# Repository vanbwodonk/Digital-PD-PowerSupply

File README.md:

# Digital USB-PD Power Supply

Low Cost USB Power Delivery adjustable power supply using CH32X035 RISC-V MCU.

- **MCU:** CH32X035G8U6 (WQFN-28), 48MHz RISC-V, USB PD PHY, USB 2.0 FS
- **Power:** USB Type-C PD (sink) → adjustable output voltage/current
- **Peripherals:** Rotary encoder control, OLED display, INA219 current sensing, USB CDC serial
- **Firmware:** C with ch32v003fun framework, PlatformIO build
- **Hardware:** Custom WQFN-28 dev board (KiCad design in `Hardware/`)

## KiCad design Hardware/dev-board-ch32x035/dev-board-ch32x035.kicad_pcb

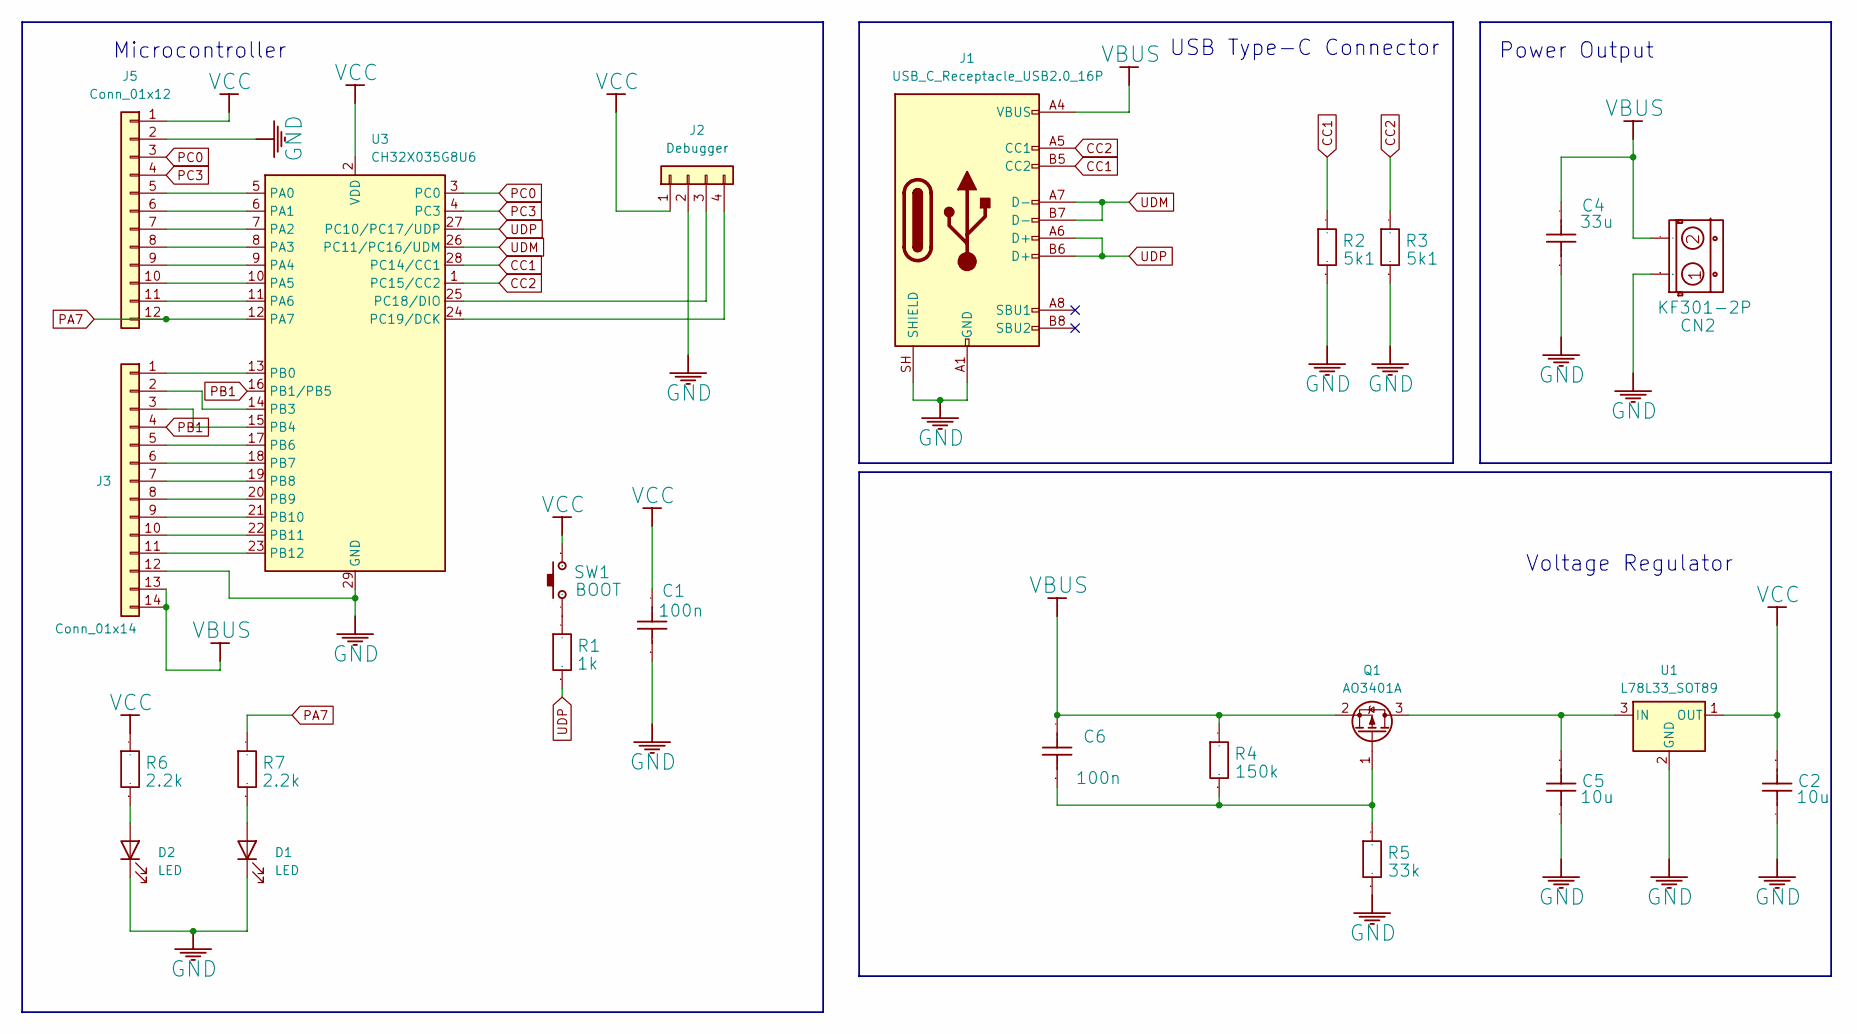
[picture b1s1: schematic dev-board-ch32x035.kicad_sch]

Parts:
C1, C6: 100n; C_0805_2012Metric; Manufacturer Part CC0603KRX7R9BB104
C2, C5: 10u; C_1206_3216Metric; Manufacturer Part CL10A106KP8NNNC
C4: 33u; C_1812_4532Metric; Manufacturer Part CC0603KRX7R9BB104
CN2: KF301-2P; TerminalBlock_Phoenix_MKDS-1,5-2-5.08_1x02_P5.08mm_Horizont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; Manufacturer Part KF301-5.0-2P
D1, D2: LED; LED_0805_2012Metric
J1: USB_C_Receptacle_USB2.0_16P; USB_C_Receptacle_GCT_USB4105-xx-A_16P_TopMnt_Horizontal
J2: Debugger; PinHeader_1x04_P2.54mm_Vertical
J3: Conn_01x14; PinHeader_1x14_P2.54mm_Vertical
J5: Conn_01x12; PinHeader_1x12_P2.54mm_Vertical
Q1: AO3401A; SOT-23
R1: 1k; R_0805_2012Metric; Manufacturer Part 0603WAF1001T5E
R2, R3: 5k1; R_0805_2012Metric; Manufacturer Part 0603WAF5101T5E
R4: 150k; R_0805_2012Metric; Manufacturer Part 0603WAF5101T5E
R5: 33k; R_0805_2012Metric; Manufacturer Part 0603WAF5101T5E
R6, R7: 2.2k; R_0805_2012Metric; Manufacturer Part 0603WAF1001T5E
SW1: BOOT; SW_Push_SPST_NO_Alps_SKRK; Manufacturer Part YTS1T0092CBG00
U1: L78L33_SOT89; SOT-89-3
U3: CH32X035G8U6; WQFN-28-1EP_4x4mm_P0.4mm_EP2.7x2.7mm

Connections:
CC1: J1.B5 (CC2), R2.2, U3.28 (PC14/CC1)
CC2: J1.A5 (CC1), R3.2, U3.1 (PC15/CC2)
GND: C1.1, C2.2, C4.1, C5.2, CN2.1, D1.1 (K), D2.1 (K), J1.A1 (GND), J1.A12 (GND), J1.B1 (GND), J1.B12 (GND), J1.SH (SHIELD), J2.2, J3.12, J5.2, R2.1, R3.1, R5.1, U1.2 (GND), U3.29 (GND)
unnamed: D1.2 (A), R7.1
unnamed: D2.2 (A), R6.1
unnamed: J2.3, U3.25 (PC18/DIO)
unnamed: J2.4, U3.24 (PC19/DCK)
unnamed: J3.1, U3.13 (PB0)
unnamed: J3.2, U3.14 (PB3)
unnamed: J3.3, U3.15 (PB4)
unnamed: J3.5, U3.17 (PB6)
unnamed: J3.6, U3.18 (PB7)
unnamed: J3.7, U3.19 (PB8)
unnamed: J3.8, U3.20 (PB9)
unnamed: J3.9, U3.21 (PB10)
unnamed: J3.10, U3.22 (PB11)
unnamed: J3.11, U3.23 (PB12)
unnamed: J5.5, U3.5 (PA0)
unnamed: J5.6, U3.6 (PA1)
unnamed: J5.7, U3.7 (PA2)
unnamed: J5.8, U3.8 (PA3)
unnamed: J5.9, U3.9 (PA4)
unnamed: J5.10, U3.10 (PA5)
unnamed: J5.11, U3.11 (PA6)
unnamed: C5.1, Q1.3 (D), U1.3 (IN)
unnamed: C6.1, Q1.1 (G), R4.1, R5.2
unnamed: R1.2, SW1.2
PA7: J5.12, R7.2, U3.12 (PA7)
PB1: J3.4, U3.16 (PB1/PB5)
PC0: J5.3, U3.3 (PC0)
PC3: J5.4, U3.4 (PC3)
UDM: J1.A7 (D-), J1.B7 (D-), U3.26 (PC11/PC16/UDM)
UDP: J1.A6 (D+), J1.B6 (D+), R1.1, U3.27 (PC10/PC17/UDP)
VBUS: C4.2, C6.2, CN2.2, J1.A4 (VBUS), J1.A9 (VBUS), J1.B4 (VBUS), J1.B9 (VBUS), J3.13, J3.14, Q1.2 (S), R4.2
VCC: C1.2, C2.1, J2.1, J5.1, R6.2, SW1.1, U1.1 (OUT), U3.2 (VDD)

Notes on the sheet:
USB Type-C Connector
Microcontroller
Voltage Regulator
Power Output

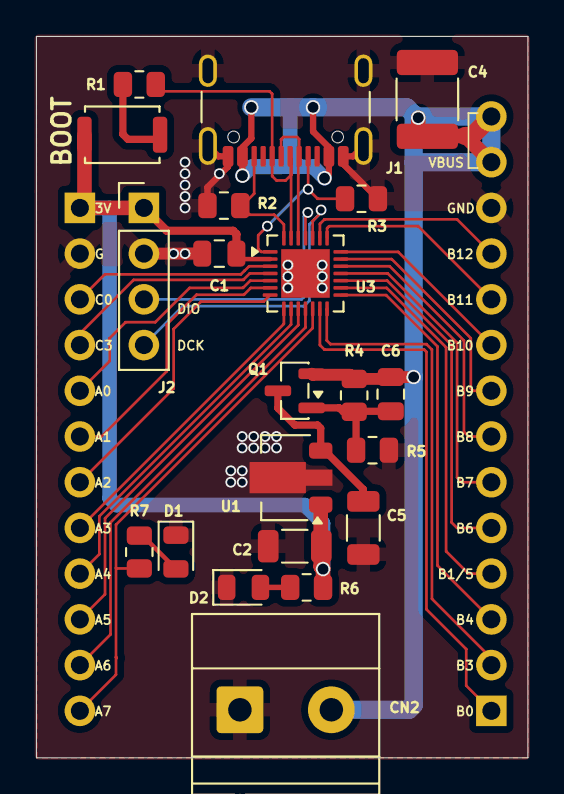
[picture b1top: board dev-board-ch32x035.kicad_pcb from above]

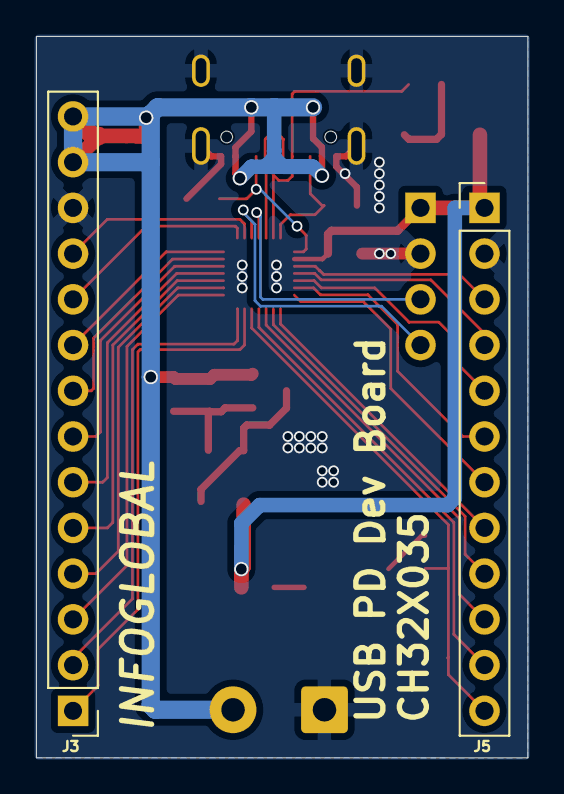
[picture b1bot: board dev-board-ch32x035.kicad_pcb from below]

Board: 2 copper layers, 27.3 x 40.1 mm, 23 parts (2 on the bottom side), 35 nets.

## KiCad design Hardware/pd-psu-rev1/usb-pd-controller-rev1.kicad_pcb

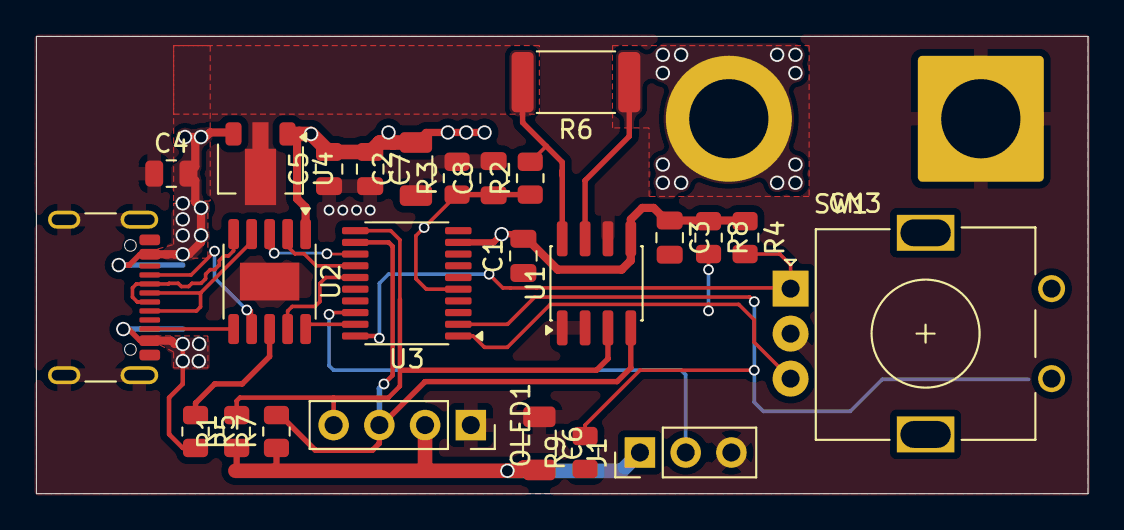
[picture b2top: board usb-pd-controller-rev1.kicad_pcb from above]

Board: 2 copper layers, 58.4 x 25.4 mm, 27 parts (1 on the bottom side), 20 nets.

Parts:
C1, C3, C5: 100n; C_0805_2012Metric
C2, C6: 10u; C_1206_3216Metric
C4: 330n; C_0805_2012Metric
C7, C8: 1U; C_0805_2012Metric
CN3: KF301-2P; SolderWire-6sqmm_1x02_P14mm_D3.5mm_OD7mm
J1: Conn_01x03; PinHeader_1x03_P2.54mm_Vertical
J2: USB_C_Receptacle_USB2.0_16P; USB_C_Receptacle_GCT_USB4105-xx-A_16P_TopMnt_Horizontal
OLED1: OLED 0.96; PinSocket_1x04_P2.54mm_Vertical
R1, R4, R7, R8, R9: 10K; R_0805_2012Metric
R2: 9.1K; R_0805_2012Metric
R3: 1K; R_0805_2012Metric
R5: 10k; R_0805_2012Metric
R6: R010; R_2512_6332Metric
SW1: RotaryEncoder_Switch; RotaryEncoder_Alps_EC11E_Vertical_H20mm
TP1: TestPoint; TestPoint_Pad_D1.5mm
U1: INA219AxD; SOIC-8_3.9x4.9mm_P1.27mm
U2: CH224K; SSOP-10-1EP_3.9x4.9mm_P1mm_EP2.1x3.3mm
U3: CH32V003FxPx; TSSOP-20_4.4x6.5mm_P0.65mm
U4: 78L33; SOT-89-3

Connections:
+3.3V: C1.2, C2.2, C3.1, C5.2, C6.2, C7.1, J1.1, OLED1.2 (VCC), R1.1, R4.1, R7.1, R8.1, R9.1, U1.5 (VS), U2.1 (VDD), U3.9 (VDD), U4.1 (Vout)
CC1: J2.A5 (CC1), U2.7 (CC1)
CC2: J2.B5 (CC2), U2.6 (CC2)
CFG1: U2.9 (CFG1), U3.15 (PC5)
CFG2: U2.2 (CFG2), U3.14 (PC4)
CFG3: U2.3 (CFG3), U3.13 (PC3)
DM: J2.A7 (D-), J2.B7 (D-), U2.5 (DM)
DP: J2.A6 (D+), J2.B6 (D+), U2.4 (DP)
GND: C1.1, C2.1, C3.2, C4.1, C5.1, C6.1, C7.2, C8.2, CN3.1, J1.3, J2.A1 (GND), J2.A12 (GND), J2.B1 (GND), J2.B12 (GND), J2.SH (SHIELD), OLED1.1 (GND), R3.2, SW1.C, U1.1 (A1), U1.2 (A0), U1.6 (GND), U2.11 (GND), U3.7 (VSS), U4.2 (GND)
unnamed: J1.2, U3.18 (PD1)
unnamed: R5.1, U2.8 (VBUS)
unnamed: C8.1, R2.1, R3.1, TP1.1 (1_1), U3.5 (PA1)
PG: U2.10 (PG), U3.19 (PD2)
ROT_A: R4.2, SW1.A, U3.20 (PD3)
ROT_B: R8.2, SW1.B, U3.1 (PD4)
ROT_PUSH: R9.2, U3.2 (PD5)
SCL: OLED1.3 (SCK), R7.2, U1.4 (SCL), U3.12 (PC2)
SDA: OLED1.4 (SDA), R1.2, U1.3 (SDA), U3.11 (PC1)
VBUS: C4.2, J2.A4 (VBUS), J2.A9 (VBUS), J2.B4 (VBUS), J2.B9 (VBUS), R2.2, R5.2, R6.2, U1.8 (IN+), U4.3 (Vin)
VOUT: CN3.2, R6.1, U1.7 (IN-)

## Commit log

2026-04-01 initial schematic
2026-04-17 moving from esp32
2026-04-17 update pcb + add some 3d files
2026-04-19 update schematic
2026-04-20 add initial ch32x035 dev board
2026-05-24 add gitignore + update readme
2026-05-24 add gitattributes
2026-05-24 add development board with CH32X035G8U6
2026-05-24 add platformio test code
2026-05-24 add usb init delay
2026-05-28 fix platformio gitignore
2026-05-28 add more test code
2026-05-28 add AGENTS.md
2026-05-31 add initial PD code
